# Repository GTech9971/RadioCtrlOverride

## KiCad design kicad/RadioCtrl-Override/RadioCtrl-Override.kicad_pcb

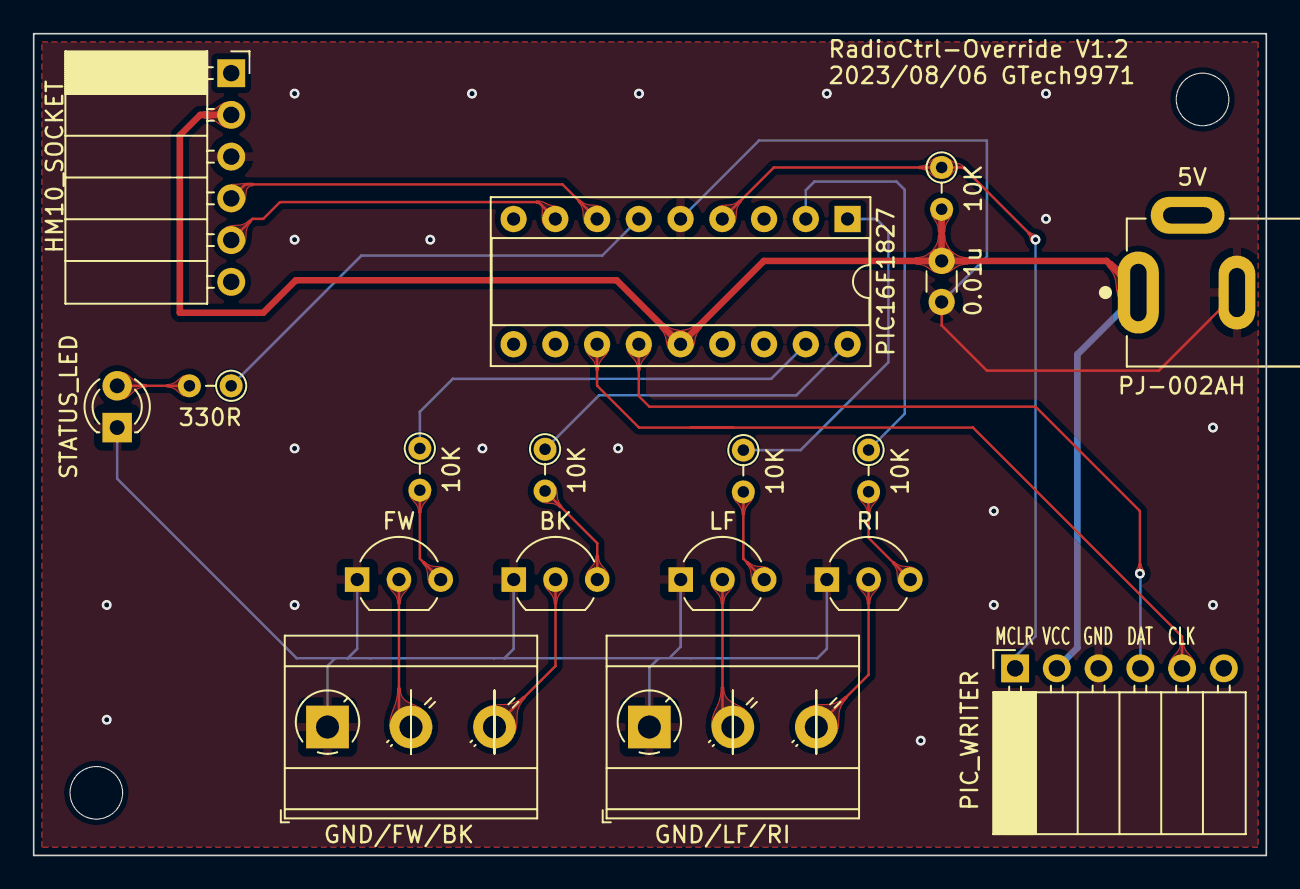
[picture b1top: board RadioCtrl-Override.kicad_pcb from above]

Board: 2 copper layers, 75.0 x 50.0 mm, 20 parts (0 on the bottom side), 21 nets.

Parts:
0.01u: 0.01u; C_Disc_D3.0mm_W1.6mm_P2.50mm
10K, 10K#2, 10K#3, 10K#4, 10K#5: 10K; R_Axial_DIN0204_L3.6mm_D1.6mm_P2.54mm_Vertical
330R: 330; R_Axial_DIN0204_L3.6mm_D1.6mm_P2.54mm_Vertical
BK: 2SC1815; TO-92_Inline_Wide
FW: 2SC1815; TO-92_Inline_Wide
GND/FW/BK: FW/BK/CON; TerminalBlock_MetzConnect_Type073_RT02603HBLU_1x03_P5.08mm_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
GND/LF/RI: LF/RI/CON; TerminalBlock_MetzConnect_Type073_RT02603HBLU_1x03_P5.08mm_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
HM10_SOCKET: HM10; PinSocket_1x06_P2.54mm_Horizontal
LF: 2SC1815; TO-92_Inline_Wide
MH1, MH2: MountingHole_3.2mm_M3
PIC16F1827: PIC16F1827-E/P; DIP-18_W7.62mm_Socket
PIC_WRITER: WRITER; PinSocket_1x06_P2.54mm_Horizontal
PJ-002AH: PJ-002AH; CUI_PJ-002AH
RI: 2SC1815; TO-92_Inline_Wide
STATUS_LED: LED_FW; LED_D3.0mm

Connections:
BK_GND: BK.2 (C), GND/FW/BK.3
BK_IN: 10K#3.1, PIC16F1827.18 (RA1/AN1/CPS1/C12IN1-/~SS2)
FW_GND: FW.2 (C), GND/FW/BK.2
FW_IN: 10K#4.1, PIC16F1827.17 (RA0/AN0/CPS0/C12IN0-/SDO2)
GND: 0.01u.1, BK.1 (E), FW.1 (E), GND/FW/BK.1, GND/LF/RI.1, HM10_SOCKET.3, LF.1 (E), PIC16F1827.5 (VSS), PIC_WRITER.3, PJ-002AH.2, RI.1 (E), STATUS_LED.1 (K)
HM10_RX: HM10_SOCKET.5, PIC16F1827.8 (RB2/AN10/CPS10/MDMIN/TX/CK/RX/DT/SDA2/S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)
HM10_TX: HM10_SOCKET.4, PIC16F1827.7 (RB1/AN11/CPS11/RX/DT/SDA1/SDI1)
ICSPCLK: PIC16F1827.12 (RB6/AN5/CPS5/T1CKI/T1OSI/P1C/CCP2/P2A/I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), PIC_WRITER.5
ICSPDAT: PIC16F1827.13 (RB7/AN6/CPS6/T1OSO/P1D/P2B/MDCIN1/ICSPD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), PIC_WRITER.4
LED_STATUS: 330R.1, PIC16F1827.6 (RB0/SRI/T1G/CCP1/P1A/INT/SRI/FLT0)
LF_GND: GND/LF/RI.2, LF.2 (C)
LF_IN: 10K#2.1, PIC16F1827.1 (RA2/AN2/CPS2/C12IN2-/C12IN+/VREF-/DACOUT)
MCLR: 10K.1, PIC16F1827.4 (RA5/~MCLR/VPP/~SS1), PIC_WRITER.1
unnamed: 330R.2, STATUS_LED.2 (A)
unnamed: 10K#4.2, FW.3 (B)
unnamed: 10K#3.2, BK.3 (B)
unnamed: 10K#2.2, LF.3 (B)
unnamed: 10K#5.2, RI.3 (B)
RI_GND: GND/LF/RI.3, RI.2 (C)
RI_IN: 10K#5.1, PIC16F1827.2 (RA3/AN3/CPS3/C12IN3-/C1IN+/VREF+/C1OUT/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)
VCC: 0.01u.2, 10K.2, HM10_SOCKET.2, PIC16F1827.14 (VDD), PIC_WRITER.2, PJ-002AH.1

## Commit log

2023-07-10 回路図作成
2023-07-12 回路図を更新
2023-07-12 pcbレイヤーを作成
2023-07-13 簡易テストプロジェクトを作成
2023-07-15 配線を実装
2023-07-15 ベタグラウンド、ビア追加
2023-07-15 FusionPCBに注文
2023-07-27 シンボルのサイズが異なっていたため修正
    コネクタとターミナル、トランジスタのサイズを変更
2023-08-06 ついにラジコンが動くプログラムを実装
    前進、後退が可能
2023-08-06 基盤の内容を修正
    ターミナルのVCCをGNDに変更
2023-08-06 プログラムを修正
